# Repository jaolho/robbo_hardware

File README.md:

# CLONE THE REPOSITORY BY CLICKING THE CLONE BUTTON IN THE UPPER RIGHT SIDE OF THE PAGE - THE ONE WITH A DOWN ARROW. #

# README #

This README would normally document whatever steps are necessary to get your application up and running.

### What is this repository for? ###

* Quick summary
* Version
* [Learn Markdown](https://bitbucket.org/tutorials/markdowndemo)

### How do I get set up? ###

* Summary of set up
* Configuration
* Dependencies
* Database configuration
* How to run tests
* Deployment instructions

### Contribution guidelines ###

* Writing tests
* Code review
* Other guidelines

### Who do I talk to? ###

* Repo owner or admin
* Other community or team contact

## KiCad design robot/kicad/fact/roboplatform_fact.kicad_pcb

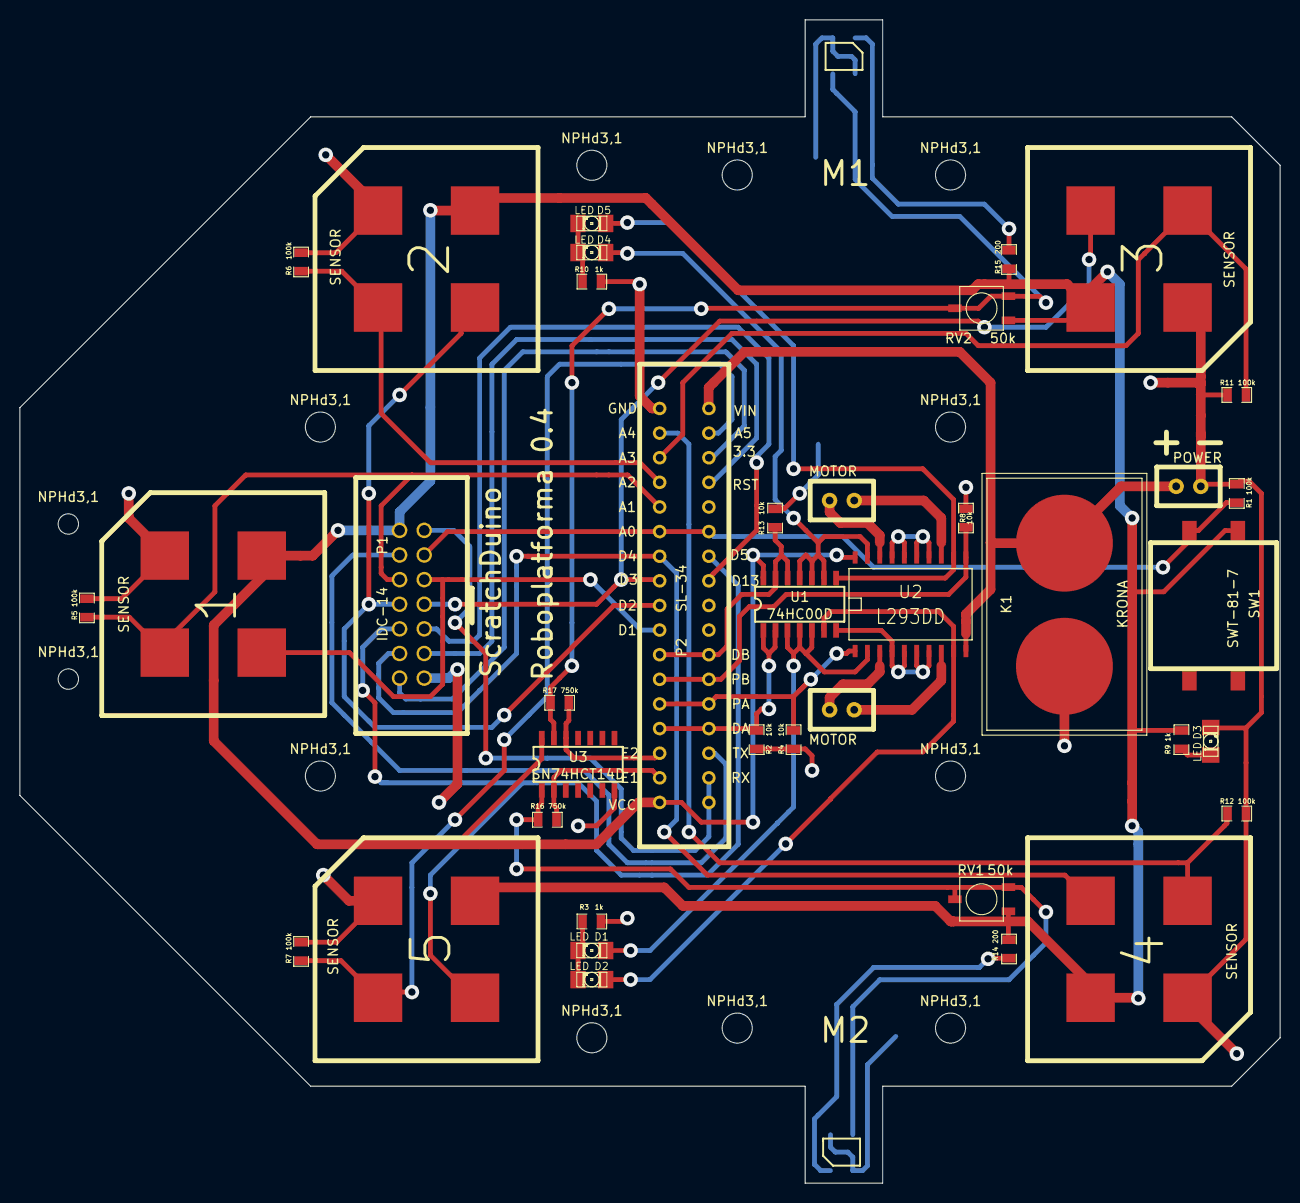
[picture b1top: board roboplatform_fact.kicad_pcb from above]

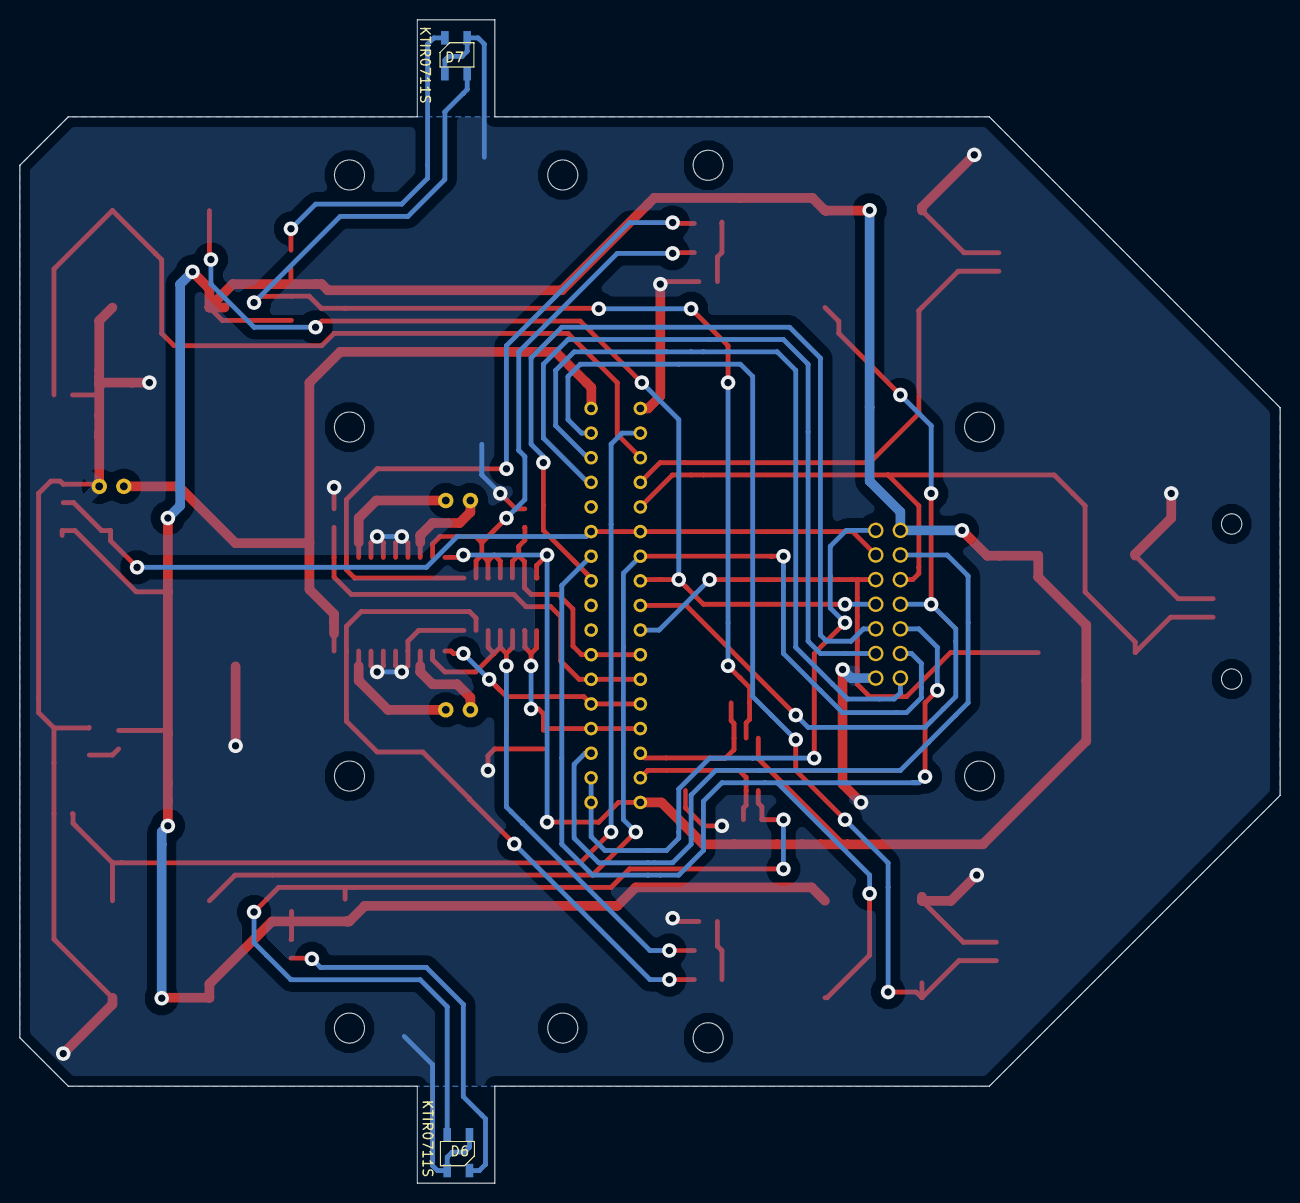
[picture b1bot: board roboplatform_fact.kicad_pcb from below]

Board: 2 copper layers, 130.0 x 120.0 mm, 53 parts (2 on the bottom side), 40 nets.

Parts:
D1, D2, D3, D4, D5: LED; LED-1206
D6, D7: KTIR0711S
K1: KRONA
NPHd3,1, NPHd3,1#2, NPHd3,1#3, NPHd3,1#4, NPHd3,1#5, NPHd3,1#6, NPHd3,1#7, NPHd3,1#8, NPHd3,1#9, NPHd3,1#10: NPHd3,1
NPHd3,1#11, NPHd3,1#12: NPHd2,1
P1: IDC-14; IDC-14M_SOCKET
P2: SL-34; SL-34_SOCKET
P3, P12: MOTOR
P6, P7, P8, P10, P11: SENSOR; SENSOR_SOCKET
P9: POWER
R1, R5, R6, R7, R11, R12: 100k; SMD0805
R2, R4, R8, R13: 10k; SMD0805
R3, R9, R10: 1k; SMD0805
R14, R15: 200; SMD0805
R16, R17: 750k; SMD0805
RV1, RV2: 50k; 3314G-1-503E
SW1: SWT-81-7
U1: 74HC00D; SOIC-14
U2: L293DD; SO20
U3: SN74HCT14D; SOIC-14

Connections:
A1: P1.10, P2.5, P6.4, R5.1
A2: P2.4, P7.4, R6.1
A3: P2.3, P10.4, R11.1
A4: P2.2, P11.4, R12.1
A5: P2.33, P8.4, R7.1
D1: P1.9, P2.10, P6.3
D2: P1.8, P2.9, P7.3
D3: P1.7, P2.8, P10.3
D4: P1.4, P2.7, P11.3
D5: P1.6, P2.28, P8.3
DIR_A: P2.14, P2.21, R2.1, U1.1, U1.2
DIR_B: P2.11, P2.24, R13.1, U1.12, U1.13
ENC1: P2.16, R16.1, U3.2
ENC2: P2.15, R17.2, U3.12
GND: D3.2, D6.2, D6.4, D7.2, D7.4, K1.2, P1.1, P2.1, P6.1, P7.1, P8.1, P9.2, P10.1, P11.1, R1.2, R2.2, R3.1, R4.1, R5.2, R6.2, R7.2, R8.2, R10.1, R11.2, R12.2, R13.2, U1.7, U2.4, U2.5, U2.6, U2.7, U2.14, U2.15, U2.16, U2.17, U3.7
unnamed: P1.12, P2.20
unnamed: P1.13, P2.18, P2.19
unnamed: P1.3, P2.31
unnamed: P1.2, P2.32
unnamed: P3.2, U2.3
unnamed: P1.11, P2.6, P2.29, R1.1, SW1.1
unnamed: P3.1, U2.8
unnamed: D1.1, U1.3, U1.4, U1.5, U2.2
unnamed: P12.1, U2.13
unnamed: P12.2, U2.18
unnamed: D4.1, U1.9, U1.10, U1.11, U2.19
unnamed: D7.1, R15.2
unnamed: D6.1, R14.2
unnamed: D2.1, U1.6, U2.9
unnamed: P1.5, P2.27
unnamed: D3.1, R9.2
unnamed: D7.3, R17.1, RV2.1, RV2.2, U3.13
unnamed: D6.3, R16.2, RV1.1, RV1.2, U3.1
unnamed: D1.2, D2.2, R3.2
unnamed: D4.2, D5.2, R10.2
unnamed: D5.1, U1.8, U2.12
PWM_A: P2.13, P2.22, R4.2, U2.1
PWM_B: P2.12, P2.23, R8.1, U2.11
VCC: P1.14, P2.17, P6.2, P7.2, P8.2, P10.2, P11.2, R9.1, R14.1, R15.1, RV1.3, RV2.3, SW1.2, U1.14, U2.20, U3.14
V_IN: K1.1, P2.34, P9.1, U2.10

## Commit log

2016-09-02 Repo created.
